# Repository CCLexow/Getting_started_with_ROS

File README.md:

# Getting_started_with_ROS
Repository containing project(s) to learn programming with ROS

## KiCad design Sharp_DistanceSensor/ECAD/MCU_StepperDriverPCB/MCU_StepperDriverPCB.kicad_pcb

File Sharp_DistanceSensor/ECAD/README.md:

# ECAD Files

Designed with [KiCad EDA](http://kicad-pcb.org)
# Credits
External 3D models:
* [TMC2100 SilentStepStick PCB](https://grabcad.com/library/tmc21x0-silentstepstick-board-1)
* [STM32 "BluePill" module](https://grabcad.com/library/stm32f103c8t6-blue-pill-board-1)

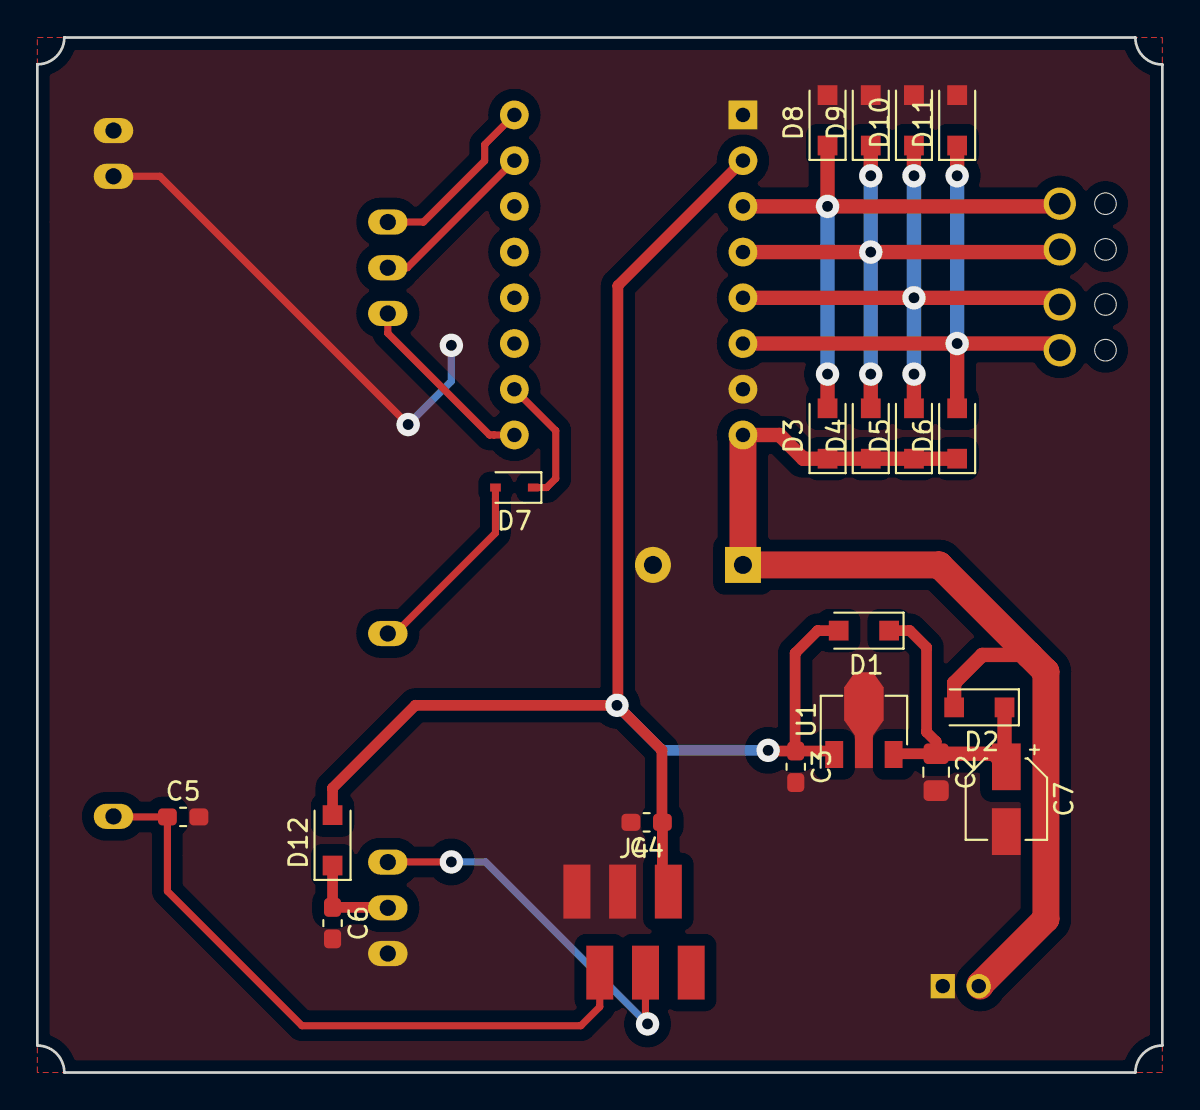
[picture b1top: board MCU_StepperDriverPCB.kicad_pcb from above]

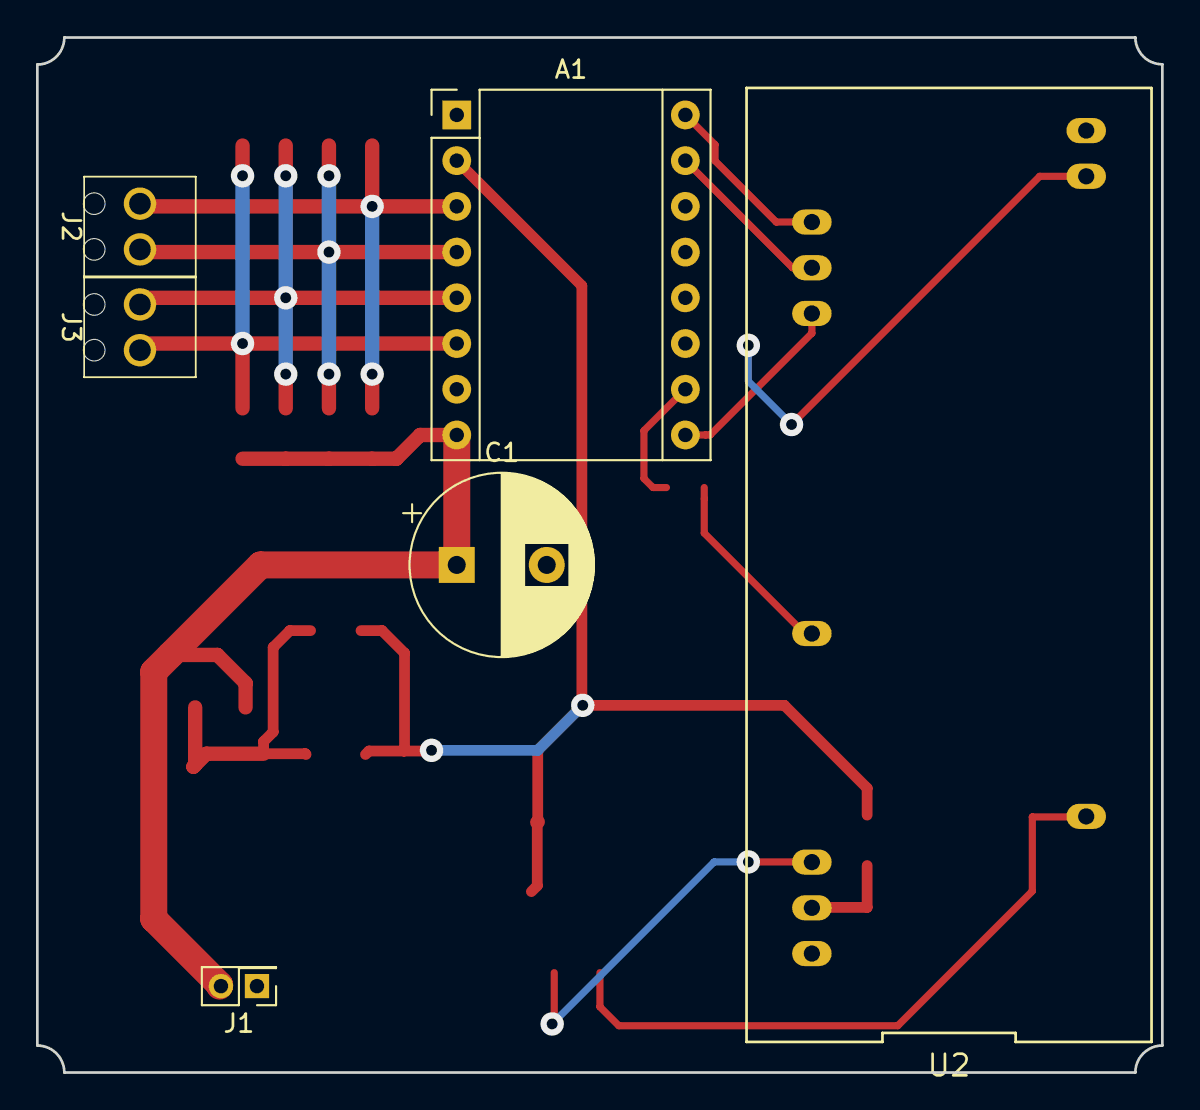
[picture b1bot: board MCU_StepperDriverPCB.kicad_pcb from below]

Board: 2 copper layers, 62.5 x 57.5 mm, 26 parts (6 on the bottom side), 16 nets.

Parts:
A1: Watterott SilentStepStick TMC2100; Pololu_Breakout-16_15.2x20.3mm
C1: 470u/25V; CP_Radial_D10.0mm_P5.00mm
C2: 1u; C_0805_2012Metric_Pad1.15x1.40mm_HandSolder
C3, C4, C5, C6: 100n; C_0603_1608Metric_Pad1.05x0.95mm_HandSolder
C7: 4u7/35V; CP_Elec_4x4.5
D1, D2, D3, D4, D5, D6, D8, D9, D10, D11, D12: NRVTS260ESFT1G; D_SOD-123F
D7: 1N4148WS; D_SOD-323
J1: Conn_01x02; PinHeader_2x01_P2.00mm_Vertical
J2, J3: Conn_01x02_Female; MPT_0,5_02_2,54
J4: Conn_01x05_Female; MM-FL-6S
U1: TA78L05F; SOT-89-3_millable_0.6mm
U2: STM32_BluePill_PortView; STM32_BluePill_ROS_GS

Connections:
+5V: A1.2, C3.1, C4.1, D1.2, D12.2, J4.5, U1.1
+12V: A1.8, C1.1, D2.2, D3.1, D4.1, D5.1, D6.1, J1.2
/AN_Distance: C5.1, J4.2, U2.5
/Light_Barrier: J4.4, U2.37
/STMD_Dir: A1.16, U2.23
/STMD_En: A1.9, U2.25
/STMD_Step: A1.15, U2.24
GND: A1.1, A1.7, C1.2, C2.2, C3.2, C4.2, C5.2, C6.2, C7.2, D8.2, D9.2, D10.2, D11.2, J1.1, J4.1, J4.3, U1.2, U2.19, U2.20, U2.39
unnamed: A1.3, D3.2, D8.1, J2.2
unnamed: A1.4, D4.2, D9.1, J2.1
unnamed: A1.5, D5.2, D10.1, J3.2
unnamed: A1.6, D6.2, D11.1, J3.1
unnamed: A1.10, D7.1
unnamed: C2.1, C7.1, D1.1, D2.1, U1.3
unnamed: C6.1, D12.1, U2.38
unnamed: D7.2, U2.32

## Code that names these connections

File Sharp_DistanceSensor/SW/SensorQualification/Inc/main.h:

/**
  ******************************************************************************
  * @file           : main.h
  * @brief          : Header for main.c file.
  *                   This file contains the common defines of the application.
  ******************************************************************************
  * This notice applies to any and all portions of this file
  * that are not between comment pairs USER CODE BEGIN and
  * USER CODE END. Other portions of this file, whether 
  * inserted by the user or by software development tools
  * are owned by their respective copyright owners.
  *
  * Copyright (c) 2018 STMicroelectronics International N.V. 
  * All rights reserved.
  *
  * Redistribution and use in source and binary forms, with or without 
  * modification, are permitted, provided that the following conditions are met:
  *
  * 1. Redistribution of source code must retain the above copyright notice, 
  *    this list of conditions and the following disclaimer.
  * 2. Redistributions in binary form must reproduce the above copyright notice,
  *    this list of conditions and the following disclaimer in the documentation
  *    and/or other materials provided with the distribution.
  * 3. Neither the name of STMicroelectronics nor the names of other 
  *    contributors to this software may be used to endorse or promote products 
  *    derived from this software without specific written permission.
  * 4. This software, including modifications and/or derivative works of this 
  *    software, must execute solely and exclusively on microcontroller or
  *    microprocessor devices manufactured by or for STMicroelectronics.
  * 5. Redistribution and use of this software other than as permitted under 
  *    this license is void and will automatically terminate your rights under 
  *    this license. 
  *
  * THIS SOFTWARE IS PROVIDED BY STMICROELECTRONICS AND CONTRIBUTORS "AS IS" 
  * AND ANY EXPRESS, IMPLIED OR STATUTORY WARRANTIES, INCLUDING, BUT NOT 
  * LIMITED TO, THE IMPLIED WARRANTIES OF MERCHANTABILITY, FITNESS FOR A 
  * PARTICULAR PURPOSE AND NON-INFRINGEMENT OF THIRD PARTY INTELLECTUAL PROPERTY
  * RIGHTS ARE DISCLAIMED TO THE FULLEST EXTENT PERMITTED BY LAW. IN NO EVENT 
  * SHALL STMICROELECTRONICS OR CONTRIBUTORS BE LIABLE FOR ANY DIRECT, INDIRECT,
  * INCIDENTAL, SPECIAL, EXEMPLARY, OR CONSEQUENTIAL DAMAGES (INCLUDING, BUT NOT
  * LIMITED TO, PROCUREMENT OF SUBSTITUTE GOODS OR SERVICES; LOSS OF USE, DATA, 
  * OR PROFITS; OR BUSINESS INTERRUPTION) HOWEVER CAUSED AND ON ANY THEORY OF 
  * LIABILITY, WHETHER IN CONTRACT, STRICT LIABILITY, OR TORT (INCLUDING 
  * NEGLIGENCE OR OTHERWISE) ARISING IN ANY WAY OUT OF THE USE OF THIS SOFTWARE,
  * EVEN IF ADVISED OF THE POSSIBILITY OF SUCH DAMAGE.
  *
  ******************************************************************************
  */

/* Define to prevent recursive inclusion -------------------------------------*/
#ifndef __MAIN_H__
#define __MAIN_H__

/* Includes ------------------------------------------------------------------*/

/* USER CODE BEGIN Includes */

/* USER CODE END Includes */

/* Private define ------------------------------------------------------------*/

#define SYS_LED_Pin GPIO_PIN_13
#define SYS_LED_GPIO_Port GPIOC
#define AN_Distance_Pin GPIO_PIN_0
#define AN_Distance_GPIO_Port GPIOA
#define STMD_Dir_Pin GPIO_PIN_14
#define STMD_Dir_GPIO_Port GPIOB
#define STMD_Step_Pin GPIO_PIN_15
#define STMD_Step_GPIO_Port GPIOB
#define STMD_En_Pin GPIO_PIN_8
#define STMD_En_GPIO_Port GPIOA
#define STMD_Cfg1_Pin GPIO_PIN_4
#define STMD_Cfg1_GPIO_Port GPIOB
#define IN_LightBarrier_Pin GPIO_PIN_9
#define IN_LightBarrier_GPIO_Port GPIOB

/* ########################## Assert Selection ############################## */
/**
  * @brief Uncomment the line below to expanse the "assert_param" macro in the 
  *        HAL drivers code
  */
/* #define USE_FULL_ASSERT    1U */

/* USER CODE BEGIN Private defines */

/* USER CODE END Private defines */

#ifdef __cplusplus
 extern "C" {
#endif
void _Error_Handler(char *, int);

#define Error_Handler() _Error_Handler(__FILE__, __LINE__)
#ifdef __cplusplus
}
#endif

#endif /* __MAIN_H__ */

/************************ (C) COPYRIGHT STMicroelectronics *****END OF FILE****/

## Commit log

2018-10-08 Commit of MCAD files for the Sharp GP2Y0A21YK0F distance sensor
2018-10-08 Cleaning up repository structure
2018-10-09 Added KiCad project for a PCB that interfaces the MCU with the sensors
2018-10-10 Updated the mechanical construction. Added a SW project to read the two sensors using an STM32 MCU
2018-10-10 Software now capable to sample the distance sensor on demand. Implemented serial command interfae to control sensor sampling.
2018-10-11 Added KiCad project for a PCB containing the MCU and the stepper motor driver for the Sharp distance sensor on stepper motor assembly
2018-10-25 MCAD: Added missing parts of sensor assembly. ECAD: updated PCB for MCU and stepper motor driver. SW: Implemented functionality to perform 360deg scans.
2018-10-25 Added readme files for the subprojets. Modified some images.
2018-10-25 Corrected MCAD readme.
2018-10-25 SW: changed task structure, implemented queues for inter-task communication
2018-10-29 SW: new task structure now functional for scanning on demand
2018-10-31 SW: Implemented continuous interleaved scanning (back and forth at different angles)
2018-10-31 SW: Added software project BluePill_SharpSensor_ROS for implementing the distance scan functionality for ROS. Initial version functional with two scan data sets for testing.
2018-11-19 SW: Changed sensor sampling from task based to DMA. Implemented homing cycle. Optimized stepper motor driving.
2018-11-19 SW: Implemented look up table and linear interpolation for the IR distance scan.
2018-11-20 SW: Implemented IR distance scan with ROS. Scanning controlled via message published by PC. Scann result transmitted in LaserScan message for 10 scans per message.
2018-11-21 SW: IR scanning is now completly controllable via ROS (homing, continuous scanning, stopping, etc.)
2018-11-28 SW: Corrected angle increment to reflect the coordinate system convention
